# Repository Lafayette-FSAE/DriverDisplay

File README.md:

# DriverDisplay
Breakout board for interfacing with and controlling the driver's display.

More information about this display can be found at https://sites.lafayette.edu/motorsports/dashboard/

The User Manual on the page linked above is very helpful when trying to understand this KiCad project

The most recent schematic is under the LEAH folder called DriverDisplay2

The most recent PCB is under the folder LEAH called DriverDisplay4

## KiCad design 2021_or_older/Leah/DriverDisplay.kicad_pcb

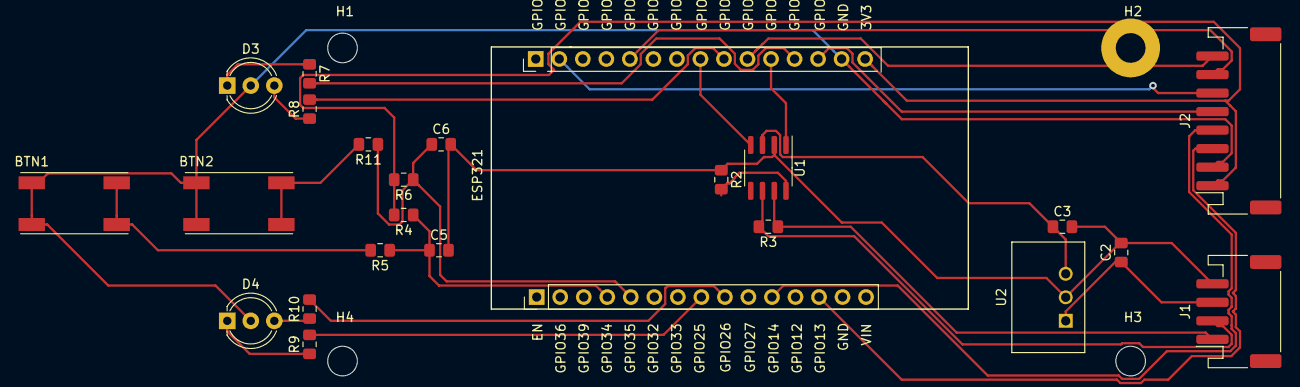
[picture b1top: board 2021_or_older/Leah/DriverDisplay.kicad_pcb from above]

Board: 2 copper layers, 27 parts (0 on the bottom side), 28 nets.

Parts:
BTN1, BTN2: PushButton
C2: 10u; C_0805_2012Metric_Pad1.15x1.40mm_HandSolder
C3: 22u; C_0805_2012Metric_Pad1.15x1.40mm_HandSolder
C5, C6: .1u; C_0805_2012Metric_Pad1.15x1.40mm_HandSolder
D3, D4: LED_Dual_ACA; LED_D5.0mm-3
ESP321: ESP32_Devkit_DOIT_V1
H1, H2, H3, H4: MountingHole; MountingHole_3.2mm_M3
J1: GLV/CAN; JST_PH_S4B-PH-SM4-TB_1x04-1MP_P2.00mm_Horizontal
J2: Display; JST_PH_S8B-PH-SM4-TB_1x08-1MP_P2.00mm_Horizontal
R2, R5, R11: 1K; R_0805_2012Metric_Pad1.15x1.40mm_HandSolder
R3: 120; R_0805_2012Metric_Pad1.15x1.40mm_HandSolder
R4, R6: 100k; R_0805_2012Metric_Pad1.15x1.40mm_HandSolder
R7, R9: 68; R_0805_2012Metric_Pad1.15x1.40mm_HandSolder
R8, R10: 750; R_0805_2012Metric_Pad1.15x1.40mm_HandSolder
U1: MCP2551-I-SN; SOIC-8_3.9x4.9mm_P1.27mm
U2: V7805-500; VX7805-500

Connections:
/BUSY: ESP321.21, J2.8
/BUTTON1: BTN1.2, R5.2
/BUTTON2: BTN2.2, R11.2
/CANRX: ESP321.23, U1.4
/CANTX: ESP321.20, U1.1
/CAN_H: J1.1, R3.1, U1.7
/CAN_L: J1.2, R3.2, U1.6
/CLK: ESP321.11, J2.4
/CS: ESP321.18, J2.5
/DC: ESP321.29, J2.6
/DIN: ESP321.13, J2.3
/ESP_3V3: ESP321.16, J2.1, R4.2, R6.2
/ESP_BUTTON1: C5.1, ESP321.4, R4.1, R5.1
/ESP_BUTTON2: C6.1, ESP321.5, R6.1, R11.1
/ESP_GND: BTN1.1, BTN2.1, D3.2, D4.2, ESP321.17, J2.2
/GLV_5V: C3.1, U1.3, U2.3
/GLV_24V: C2.1, J1.3, U2.1
/GLV_RTN: C2.2, C3.2, C5.2, C6.2, J1.4, R2.1, U1.2, U2.2
/RST: ESP321.26, J2.7
/~G1: ESP321.22, R8.2
/~G2: ESP321.9, R10.2
/~R1: ESP321.19, R7.2
/~R2: ESP321.8, R9.2
unnamed: D3.1, R7.1
unnamed: D3.3, R8.1
unnamed: D4.1, R9.1
unnamed: D4.3, R10.1
unnamed: R2.2, U1.8

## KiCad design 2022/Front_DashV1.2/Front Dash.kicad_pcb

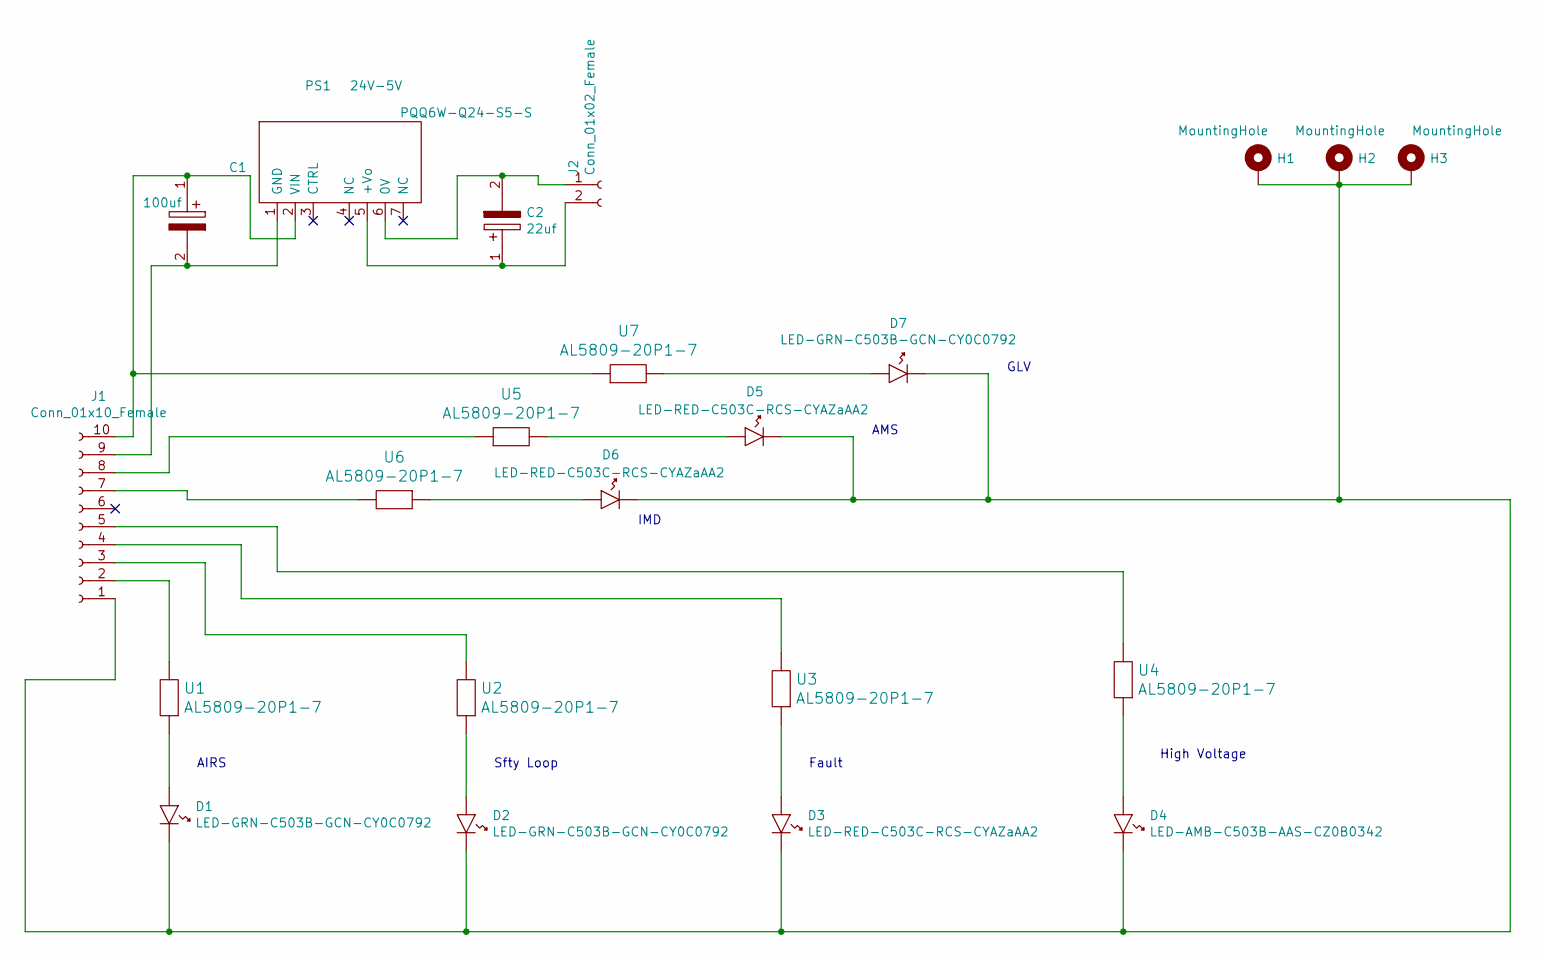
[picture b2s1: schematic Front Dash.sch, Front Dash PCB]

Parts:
C1: 100uf; EEETC1V470P; Mouser Part Number 667-EEE-FK1H101L
C2: 22uf; CAPAE660X565N; Mouser Part Number 80-EEV226M050A9GAA
D1, D2, D7: LED-GRN-C503B-GCN-CY0C0792; LED_D5.0mm
D3, D5, D6: LED-RED-C503C-RCS-CYAZaAA2; LED_D5.0mm
D4: LED-AMB-C503B-AAS-CZ0B0342; LED_D5.0mm
H1, H2, H3: MountingHole; MountingHole_2.2mm_M2_Pad
J1: Conn_01x10_Female; Molex_SPOX_5267-10A_1x10_P2.50mm_Vertical
J2: Conn_01x02_Female; Molex_SPOX_5267-02A_1x02_P2.50mm_Vertical
PS1: 24V-5V; PQQ6W-Q24-S5-S
U1, U2, U3, U4, U5, U6, U7: AL5809-20P1-7; AL5809-60P1-7

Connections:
unnamed: C1.1, J1.10, PS1.2 (VIN), U7.1
unnamed: C1.2, J1.9, PS1.1 (GND)
unnamed: C2.1, J2.2, PS1.5 (+Vo)
unnamed: C2.2, J2.1, PS1.6 (0V)
unnamed: D1.1, U1.1
unnamed: D1.2, D2.2, D3.2, D4.2, D5.2, D6.2, D7.2, H1.1, H2.1, H3.1, J1.1
unnamed: D2.1, U2.1
unnamed: D3.1, U3.1
unnamed: D4.1, U4.1
unnamed: D5.1, U5.2
unnamed: D6.1, U6.1
unnamed: D7.1, U7.2
unnamed: J1.2, U1.2
unnamed: J1.3, U2.2
unnamed: J1.4, U3.2
unnamed: J1.5, U4.2
unnamed: J1.7, U6.2
unnamed: J1.8, U5.1

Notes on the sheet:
AIRS
Sfty Loop
Fault
High Voltage
GLV
AMS
IMD

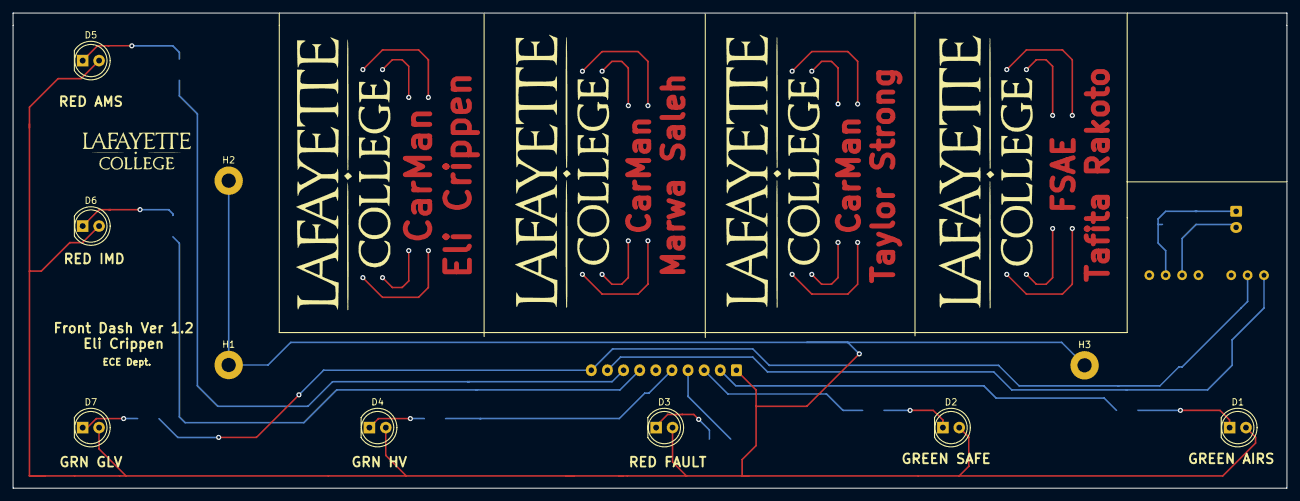
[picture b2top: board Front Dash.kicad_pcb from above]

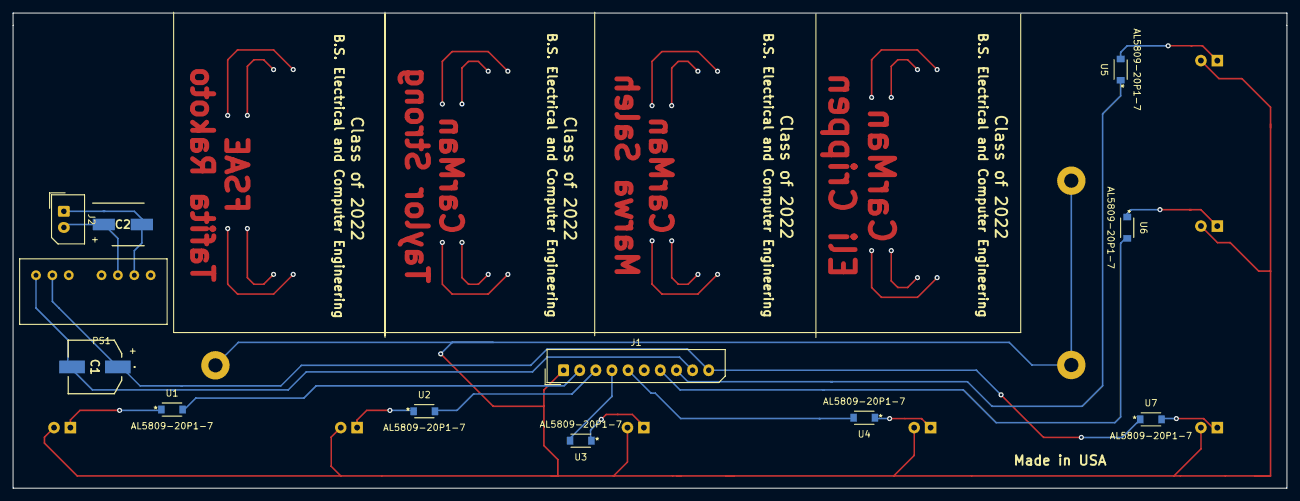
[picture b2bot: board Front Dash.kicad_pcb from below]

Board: 2 copper layers, 197.5 x 73.7 mm, 22 parts (12 on the bottom side), 18 nets.

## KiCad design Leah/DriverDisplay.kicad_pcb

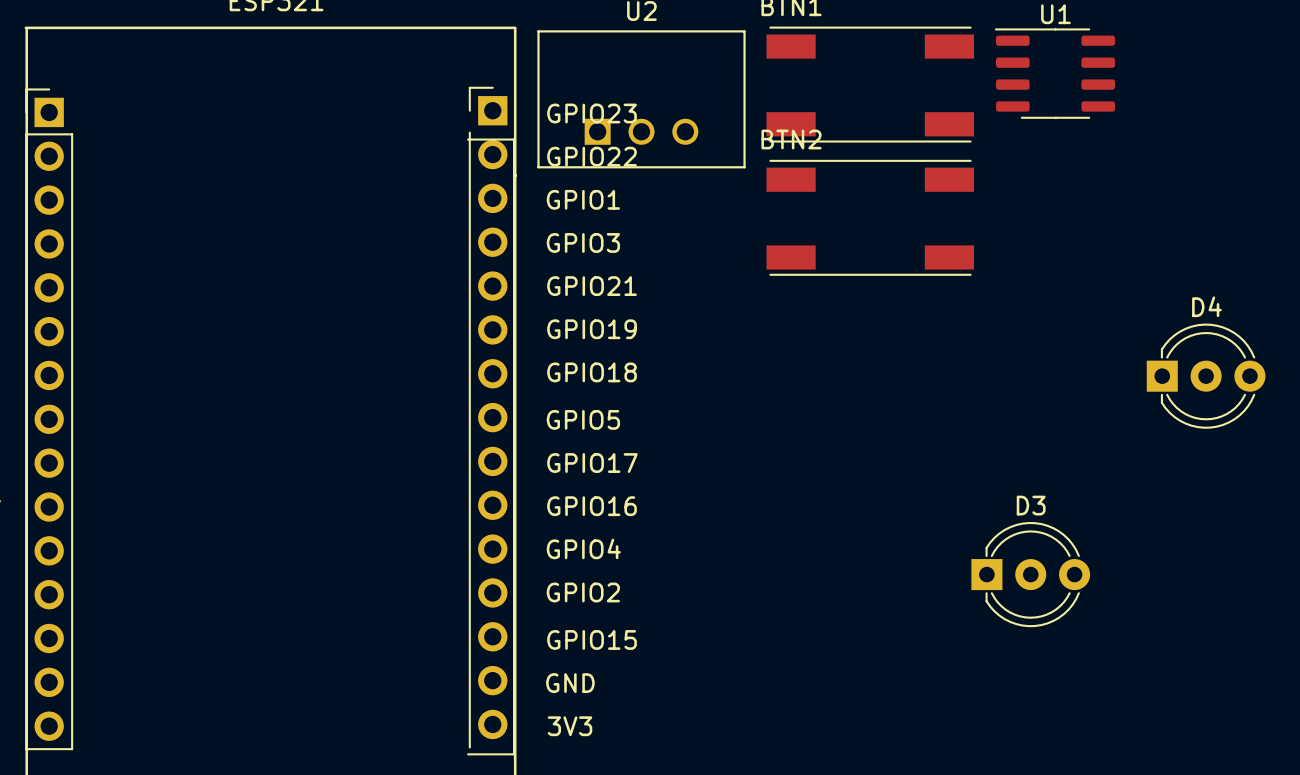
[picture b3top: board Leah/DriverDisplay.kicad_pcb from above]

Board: 2 copper layers, 7 parts (0 on the bottom side), 3 nets, no tracks yet.

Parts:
BTN1, BTN2: PushButton
D3, D4: LED_Dual_ACA; LED_D5.0mm-3
ESP321: ESP32_Devkit_DOIT_V1
U1: MCP2551-I-SN; SOIC-8_3.9x4.9mm_P1.27mm
U2: V7805-500; VX7805-500

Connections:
/ESP_GND: D3.2, D4.2, ESP321.17
/GLV_5V: U1.3, U2.3
/GLV_RTN: U1.2, U2.2

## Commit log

2019-11-20 First quick project creation
2019-11-22 Added back in CAN transceiver, also some RGB LEDs
2020-02-04 starting new design for dash
2020-02-04 added kicad library
2020-02-18 added kicad designs
2020-02-19 updated dashboard 2.0
2020-03-06 added new versions of board
2020-03-09 v4 board
2020-03-10 fixed mounting holes
2020-03-13 added ams
2022-03-08 Changed LEDs and organized folders, libraries
2022-03-22 Added Documentation

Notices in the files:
parts and their libraries:
Copyright 2016 Accelerated Designs. All rights reserved.
